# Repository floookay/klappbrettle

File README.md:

> [!CAUTION]
> This is still a work in progress and not yet fully tested! I messed up my last order from Mouser and need to get the missing components the next time I get to order.

# klappbrettle

a 40% ortho keyboard with a hinge

## design

I love using ortho keyboards but non-split ortho keyboards are getting uncomfortable for me fast so I thought about adding a hinge at the top.

It kind of resembles a starter clapper so that's where it got its name and athletics theme.

## pcb

PCBWay ([PCBWay.com](https://pcbway.com)) kindly offered to sponsor the pcb for this project that's why I got my hands on the pcbs within almost a week after ordering.  
The order process is straight forward and you also get an instant quote before ordering. After placing the order a technician checked and corrected the drill holes of the mouse bits within a few hours and the pcb was sent to manufacturing.
I'm impressed with the speed an quality of the pcb, see below:

The pcb is a two panel design where both sides are connected via a 10 pin JST connector. It's powered by a RP2040 microcontroller so there is plenty of flash storage. You can clip off the mod columns or the outer thumb key if want to. There are also extra holes where you can put grommets so the switches don't pop out of the 3mm plate.

- [x] complete the pcb design
- [ ] order missing components and solder

## case

The case is a 3mm acryl sandwich style case with a hinge to connect the halves and route the cable through. The hinge can be either 3d printed or can be 3mm acryl as well. I still need to test what works best, so far I only have a 3d printed prototype at hand.

- [x] complete the acrylic case design
- [ ] make the bottom plates look a bit nicer
- [ ] prepare dxf files and variants for laser cutting

## firmware

This will be powered by QMK but the firmware isn't ready yet.

- [x] finish [qmk firmware](https://github.com/floookay/qmk_firmware/tree/klappbrettle)
- [ ] add vial support

## acknowledgements

Huge thanks to PCBWay for offering to sponsor this project, hlord2000 for their [RP2040 KiCAD template](https://github.com/hlord2000/Ohmbedded-RP2040-PCB-Template) as well as the ClackTales community for helping me with the theme.

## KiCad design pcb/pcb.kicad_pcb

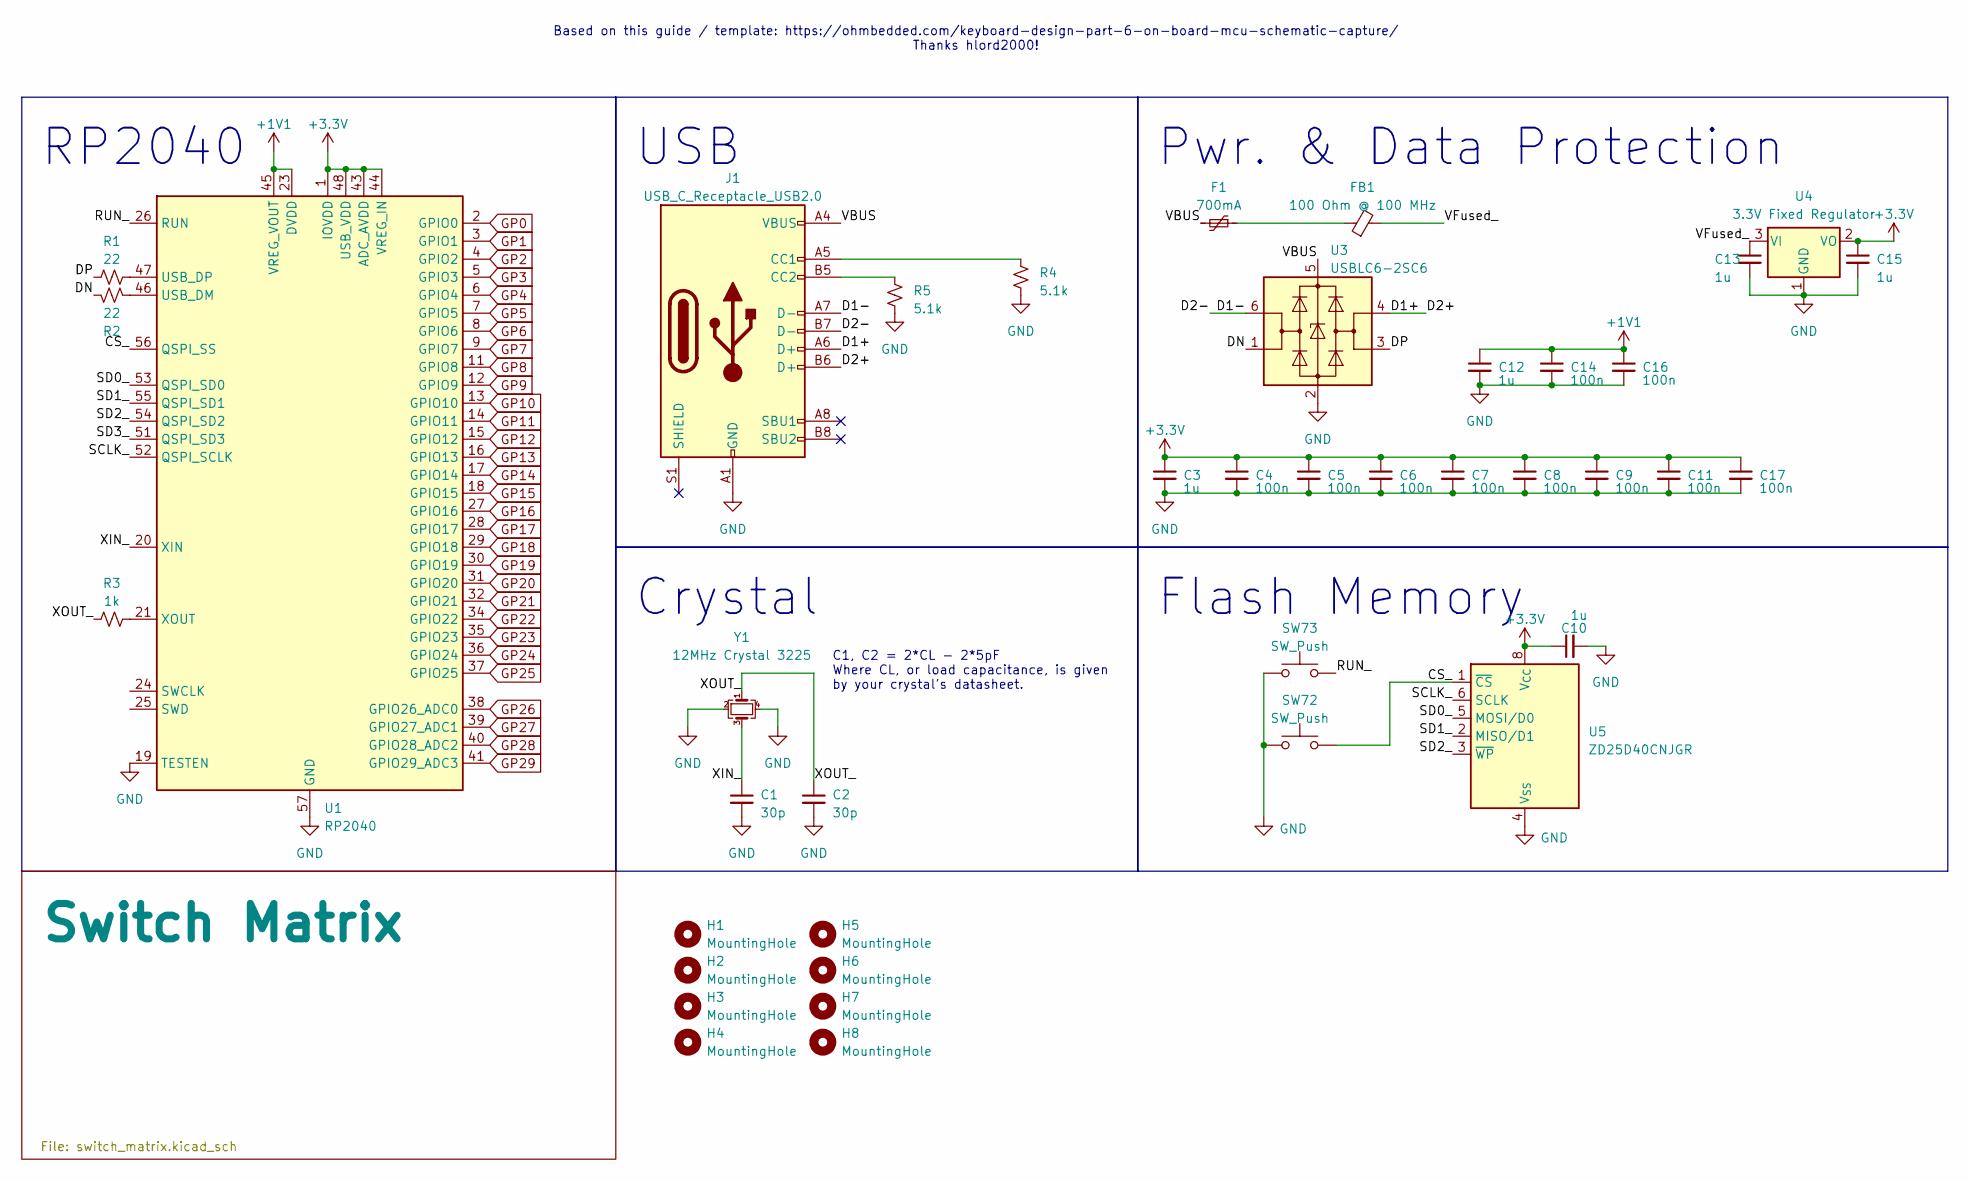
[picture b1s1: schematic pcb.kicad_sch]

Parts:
C1, C2: 30p; C_0402_1005Metric; LCSC C1562
C3, C10, C12, C13, C15: 1u; C_0402_1005Metric; LCSC C52923
C4, C5, C6, C7, C8, C9, C11, C14, C16, C17: 100n; C_0402_1005Metric; LCSC C1525
F1: 700mA; Fuse_0402_1005Metric; LCSC C914086
FB1: 100 Ohm @ 100 MHz; L_0402_1005Metric; LCSC C85812
H1, H2, H3, H4, H5, H6, H7, H8: MountingHole; spacer_hole_4mm
J1: USB_C_Receptacle_USB2.0; USB_C_Receptacle_GCT_USB4110
R1, R2: 22; R_0402_1005Metric; LCSC C25152
R3: 1k; R_0402_1005Metric; LCSC C106235
R4, R5: 5.1k; R_0402_1005Metric; LCSC C25905
SW72, SW73: SW_Push; SW_SPST_SKQG_WithoutStem; LCSC C115351
U1: RP2040; QFN-56-1EP_7x7mm_P0.4mm_EP3.2x3.2mm_ThermalVias; LCSC C2040
U3: USBLC6-2SC6; SOT-23-6; LCSC C558442
U4: 3.3V Fixed Regulator; TSOT-23; LCSC C150715
U5: ZD25D40CNJGR; USON-8_1.5x1.5mm_P0.45mm; LCSC C3646778
Y1: 12MHz Crystal 3225; Crystal_SMD_3225-4Pin_3.2x2.5mm; LCSC C9002

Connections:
+1V1: C12.1, C14.1, C16.1, U1.23 (DVDD), U1.45 (VREG_VOUT), U1.50 (DVDD)
+3.3V: C3.1, C4.1, C5.1, C6.1, C7.1, C8.1, C9.1, C10.1, C11.1, C15.1, C17.1, U1.1 (IOVDD), U1.10 (IOVDD), U1.22 (IOVDD), U1.33 (IOVDD), U1.42 (IOVDD), U1.43 (ADC_AVDD), U1.44 (VREG_IN), U1.48 (USB_VDD), U1.49 (IOVDD), U4.2 (VO), U5.8 (V_{CC})
/CS_: SW72.2, U1.56 (QSPI_SS), U5.1 (~CS)
/D1+: J1.A6 (D+), J1.B6 (D+), U3.4 (I/O2)
/D1-: J1.A7 (D-), J1.B7 (D-), U3.6 (I/O1)
/DN: R2.2, U3.1 (I/O1)
/DP: R1.1, U3.3 (I/O2)
/RUN_: SW73.2, U1.26 (RUN)
/SCLK_: U1.52 (QSPI_SCLK), U5.6 (SCLK)
/SD0_: U1.53 (QSPI_SD0), U5.5 (MOSI/D0)
/SD1_: U1.55 (QSPI_SD1), U5.2 (MISO/D1)
/SD2_: U1.54 (QSPI_SD2), U5.3 (~WP)
/SD3_: U1.51 (QSPI_SD3)
/VBUS: F1.2, J1.A4 (VBUS), J1.A9 (VBUS), J1.B4 (VBUS), J1.B9 (VBUS), U3.5 (VBUS)
/VFused_: C13.1, FB1.2, U4.3 (VI)
/XIN_: C1.1, U1.20 (XIN), Y1.3
/XOUT_: C2.1, R3.1, Y1.1
GND: C1.2, C2.2, C3.2, C4.2, C5.2, C6.2, C7.2, C8.2, C9.2, C10.2, C11.2, C12.2, C13.2, C14.2, C15.2, C16.2, C17.2, J1.A1 (GND), J1.A12 (GND), J1.B1 (GND), J1.B12 (GND), R4.1, R5.1, SW72.1, SW73.1, U1.19 (TESTEN), U1.57 (GND), U3.2 (GND), U4.1 (GND), U5.4 (V_{SS}), U5.9 (PAD/V_{SS}), Y1.2, Y1.4
GP0: U1.2 (GPIO0)
GP1: U1.3 (GPIO1); also elsewhere on the board
GP2: U1.4 (GPIO2); also elsewhere on the board
GP3: U1.5 (GPIO3); also elsewhere on the board
GP4: U1.6 (GPIO4); also elsewhere on the board
GP5: U1.7 (GPIO5); also elsewhere on the board
GP6: U1.8 (GPIO6); also elsewhere on the board
GP7: U1.9 (GPIO7)
GP8: U1.11 (GPIO8)
GP9: U1.12 (GPIO9)
GP10: U1.13 (GPIO10)
GP11: U1.14 (GPIO11); also elsewhere on the board
GP12: U1.15 (GPIO12); also elsewhere on the board
GP13: U1.16 (GPIO13); also elsewhere on the board
GP14: U1.17 (GPIO14); also elsewhere on the board
GP15: U1.18 (GPIO15); also elsewhere on the board
GP16: U1.27 (GPIO16); also elsewhere on the board
GP17: U1.28 (GPIO17)
GP18: U1.29 (GPIO18)
GP19: U1.30 (GPIO19)
GP20: U1.31 (GPIO20)
GP21: U1.32 (GPIO21)
GP22: U1.34 (GPIO22)
GP23: U1.35 (GPIO23); also elsewhere on the board
GP24: U1.36 (GPIO24); also elsewhere on the board
GP25: U1.37 (GPIO25)
GP26: U1.38 (GPIO26_ADC0)
GP27: U1.39 (GPIO27_ADC1)
GP28: U1.40 (GPIO28_ADC2); also elsewhere on the board
GP29: U1.41 (GPIO29_ADC3); also elsewhere on the board
unnamed: F1.1, FB1.1
unnamed: J1.A5 (CC1), R4.2
unnamed: J1.B5 (CC2), R5.2
unnamed: R2.1, U1.46 (USB_DM)
unnamed: R1.2, U1.47 (USB_DP)
unnamed: R3.2, U1.21 (XOUT)

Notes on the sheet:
Flash Memory
Pwr. & Data Protection
Based on this guide / template: https://ohmbedded.com/keyboard-design-part-6-on-board-mcu-schematic-capture/ Thanks hlord2000!
C1, C2 = 2*CL - 2*5pF Where CL, or load capacitance, is given by your crystal's datasheet.
Crystal
RP2040
USB

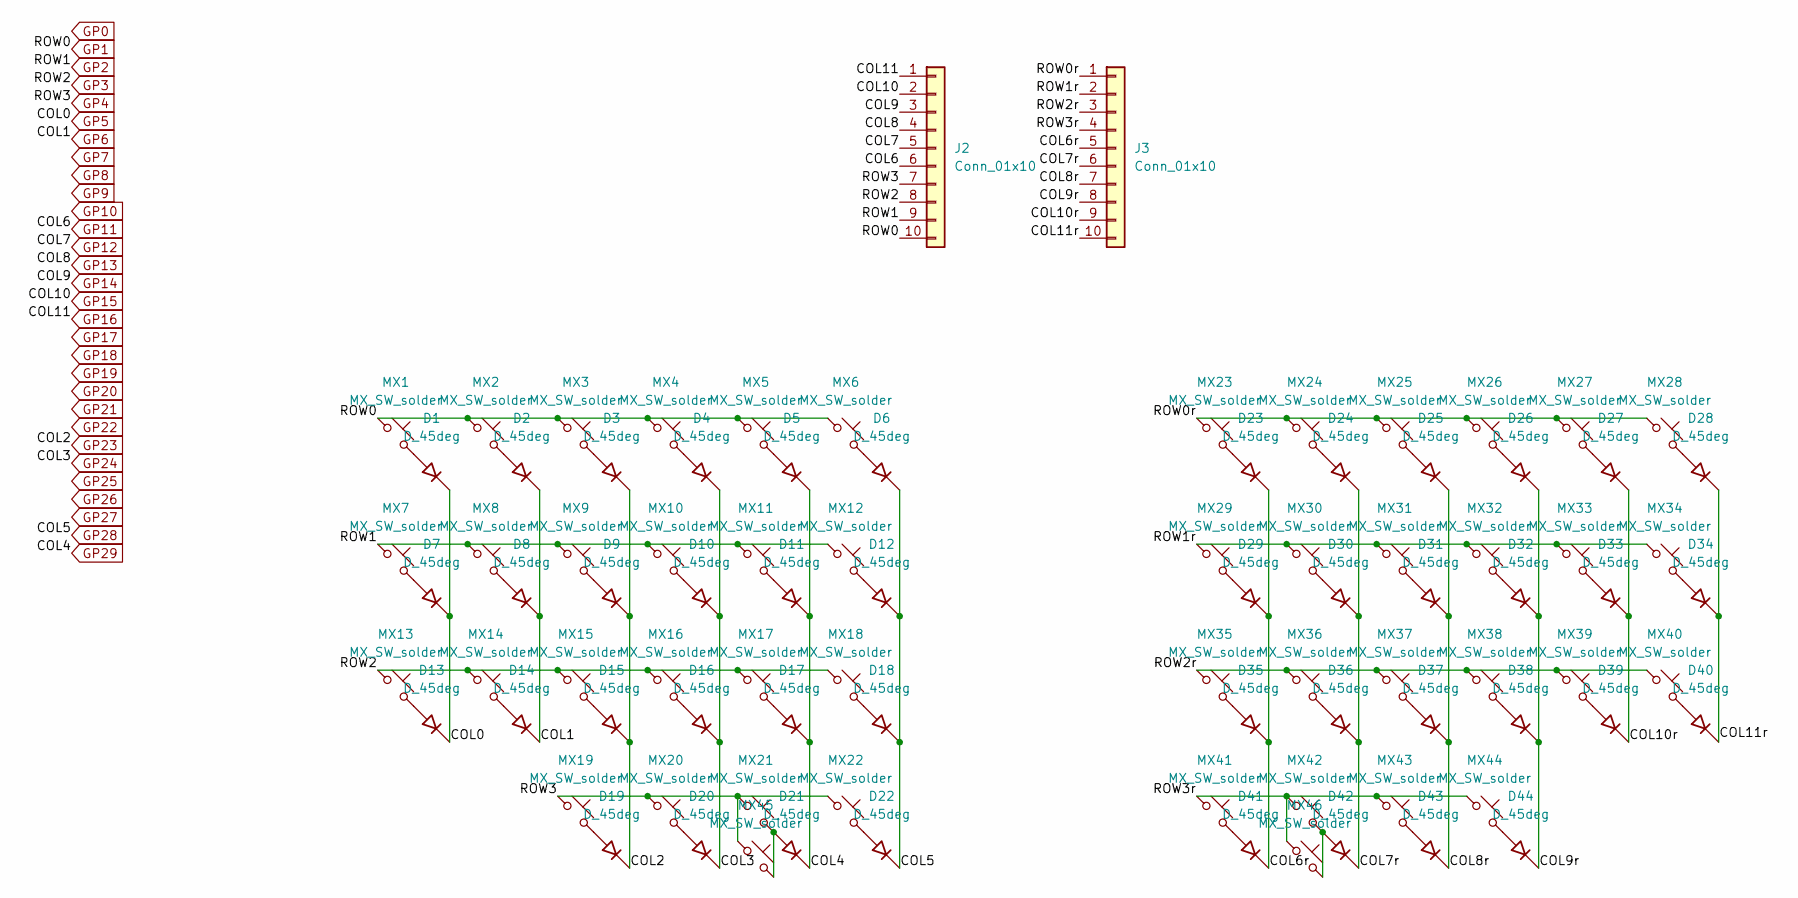
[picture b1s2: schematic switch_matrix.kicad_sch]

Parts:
D1, D2, D3, D4, D5, D6, D7, D8, D9, D10, D11, D12, D13, D14, D15, D16, D17, D18, D19, D20, D21, D22, D23, D24, D25, D26, D27, D28, D29, D30, D31, D32, D33, D34, D35, D36, D37, D38, D39, D40, D41, D42, D43, D44: D_45deg; D_SOD-123-minimal
J2, J3: Conn_01x10; JST_GH_SM10B-GHS-TB_1x10-1MP_P1.25mm_Horizontal
MX1, MX2, MX3, MX4, MX5, MX6, MX7, MX8, MX9, MX10, MX11, MX12, MX13, MX14, MX15, MX16, MX17, MX18, MX19, MX20, MX21, MX22, MX23, MX24, MX25, MX26, MX27, MX28, MX29, MX30, MX31, MX32, MX33, MX34, MX35, MX36, MX37, MX38, MX39, MX40, MX41, MX42, MX43, MX44, MX45, MX46: MX_SW_solder; SW_MX_1u

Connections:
/Switch Matrix/COL6r: D23.1 (K), D29.1 (K), D35.1 (K), D41.1 (K), J3.5
/Switch Matrix/COL7r: D24.1 (K), D30.1 (K), D36.1 (K), D42.1 (K), J3.6
/Switch Matrix/COL8r: D25.1 (K), D31.1 (K), D37.1 (K), D43.1 (K), J3.7
/Switch Matrix/COL9r: D26.1 (K), D32.1 (K), D38.1 (K), D44.1 (K), J3.8
/Switch Matrix/COL10r: D27.1 (K), D33.1 (K), D39.1 (K), J3.9
/Switch Matrix/COL11r: D28.1 (K), D34.1 (K), D40.1 (K), J3.10
/Switch Matrix/ROW0r: J3.1, MX23.1, MX24.1, MX25.1, MX26.1, MX27.1, MX28.1
/Switch Matrix/ROW1r: J3.2, MX29.1, MX30.1, MX31.1, MX32.1, MX33.1, MX34.1
/Switch Matrix/ROW2r: J3.3, MX35.1, MX36.1, MX37.1, MX38.1, MX39.1, MX40.1
/Switch Matrix/ROW3r: J3.4, MX41.1, MX42.1, MX43.1, MX44.1, MX46.1
GP1: J2.10, MX1.1, MX2.1, MX3.1, MX4.1, MX5.1, MX6.1; also elsewhere on the board
GP2: J2.9, MX7.1, MX8.1, MX9.1, MX10.1, MX11.1, MX12.1; also elsewhere on the board
GP3: J2.8, MX13.1, MX14.1, MX15.1, MX16.1, MX17.1, MX18.1; also elsewhere on the board
GP4: J2.7, MX19.1, MX20.1, MX21.1, MX22.1, MX45.1; also elsewhere on the board
GP5: D1.1 (K), D7.1 (K), D13.1 (K); also elsewhere on the board
GP6: D2.1 (K), D8.1 (K), D14.1 (K); also elsewhere on the board
GP11: J2.6; also elsewhere on the board
GP12: J2.5; also elsewhere on the board
GP13: J2.4; also elsewhere on the board
GP14: J2.3; also elsewhere on the board
GP15: J2.2; also elsewhere on the board
GP16: J2.1; also elsewhere on the board
GP23: D3.1 (K), D9.1 (K), D15.1 (K), D19.1 (K); also elsewhere on the board
GP24: D4.1 (K), D10.1 (K), D16.1 (K), D20.1 (K); also elsewhere on the board
GP28: D6.1 (K), D12.1 (K), D18.1 (K), D22.1 (K); also elsewhere on the board
GP29: D5.1 (K), D11.1 (K), D17.1 (K), D21.1 (K); also elsewhere on the board
unnamed: D1.2 (A), MX1.2
unnamed: D2.2 (A), MX2.2
unnamed: D3.2 (A), MX3.2
unnamed: D4.2 (A), MX4.2
unnamed: D5.2 (A), MX5.2
unnamed: D6.2 (A), MX6.2
unnamed: D7.2 (A), MX7.2
unnamed: D8.2 (A), MX8.2
unnamed: D9.2 (A), MX9.2
unnamed: D10.2 (A), MX10.2
unnamed: D11.2 (A), MX11.2
unnamed: D12.2 (A), MX12.2
unnamed: D13.2 (A), MX13.2
unnamed: D14.2 (A), MX14.2
unnamed: D15.2 (A), MX15.2
unnamed: D16.2 (A), MX16.2
unnamed: D17.2 (A), MX17.2
unnamed: D18.2 (A), MX18.2
unnamed: D19.2 (A), MX19.2
unnamed: D20.2 (A), MX20.2
unnamed: D21.2 (A), MX21.2, MX45.2
unnamed: D22.2 (A), MX22.2
unnamed: D23.2 (A), MX23.2
unnamed: D24.2 (A), MX24.2
unnamed: D25.2 (A), MX25.2
unnamed: D26.2 (A), MX26.2
unnamed: D27.2 (A), MX27.2
unnamed: D28.2 (A), MX28.2
unnamed: D29.2 (A), MX29.2
unnamed: D30.2 (A), MX30.2
unnamed: D31.2 (A), MX31.2
unnamed: D32.2 (A), MX32.2
unnamed: D33.2 (A), MX33.2
unnamed: D34.2 (A), MX34.2
unnamed: D35.2 (A), MX35.2
unnamed: D36.2 (A), MX36.2
unnamed: D37.2 (A), MX37.2
unnamed: D38.2 (A), MX38.2
unnamed: D39.2 (A), MX39.2
unnamed: D40.2 (A), MX40.2
unnamed: D41.2 (A), MX41.2
unnamed: D42.2 (A), MX42.2, MX46.2
unnamed: D43.2 (A), MX43.2
unnamed: D44.2 (A), MX44.2

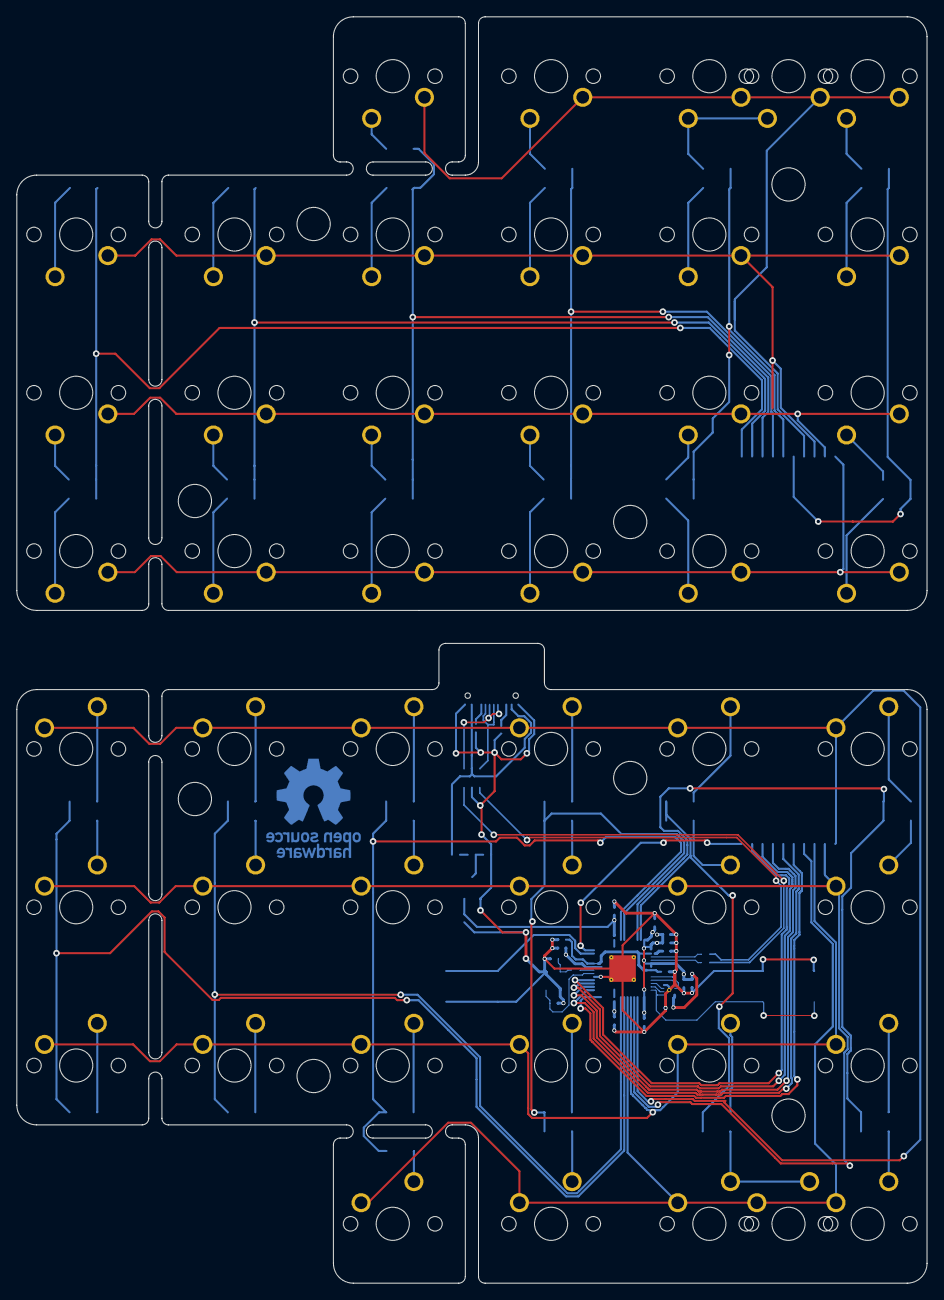
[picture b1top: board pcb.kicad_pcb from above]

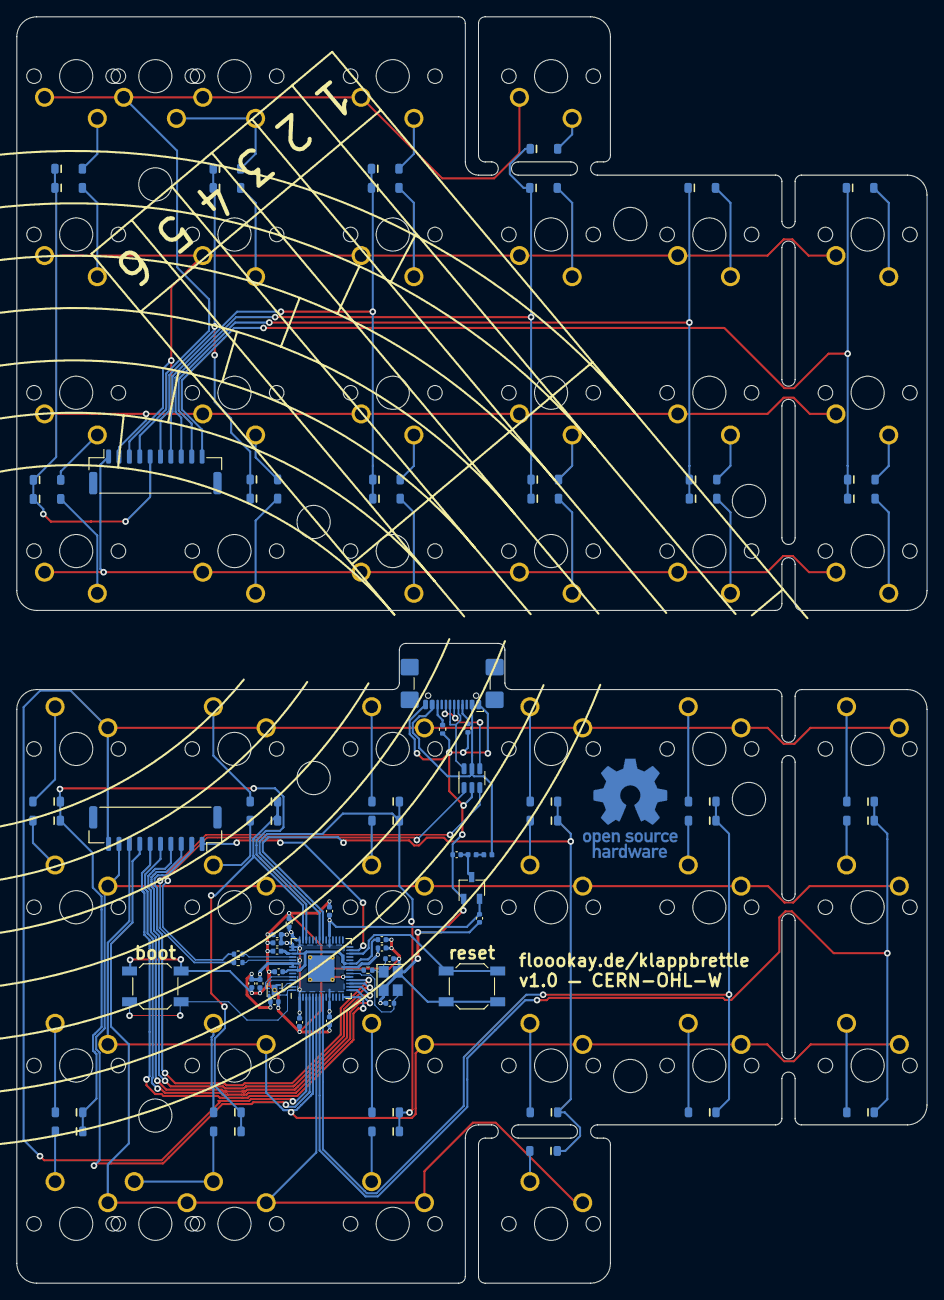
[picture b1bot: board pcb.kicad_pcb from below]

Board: 4 copper layers, 109.5 x 152.4 mm, 132 parts (78 on the bottom side), 93 nets.

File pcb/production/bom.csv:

Designator,Footprint,Quantity,Value,LCSC Part #
"C1, C2",0402,2,30p,C1562
"C10, C12, C13, C15, C3",0402,5,1u,C52923
"C11, C14, C16, C17, C4, C5, C6, C7, C8, C9",0402,10,100n,C1525
"D1, D10, D11, D12, D13, D14, D15, D16, D17, D18, D19, D2, D20, D21, D22, D23, D24, D25, D26, D27, D28, D29, D3, D30, D31, D32, D33, D34, D35, D36, D37, D38, D39, D4, D40, D41, D42, D43, D44, D5, D6, D7, D8, D9",D_SOD-123-minimal,44,D_45deg,
F1,0402,1,700mA,C914086
FB1,0402,1,100 Ohm @ 100 MHz,C85812
J1,USB_C_Receptacle_GCT_USB4110,1,USB_C_Receptacle_USB2.0,C9002
"J2, J3",JST_GH_SM10B-GHS-TB_1x10-1MP_P1.25mm_Horizontal,2,Conn_01x10,C2683602
"MX1, MX10, MX11, MX12, MX13, MX14, MX15, MX16, MX17, MX18, MX19, MX2, MX20, MX21, MX22, MX23, MX24, MX25, MX26, MX27, MX28, MX29, MX3, MX30, MX31, MX32, MX33, MX34, MX35, MX36, MX37, MX38, MX39, MX4, MX40, MX41, MX42, MX43, MX44, MX45, MX46, MX5, MX6, MX7, MX8, MX9",SW_MX_1u,46,MX_SW_solder,
"R1, R2",0402,2,22,C25152
R3,0402,1,1k,C106235
"R4, R5",0402,2,5.1k,C25905
"S1, S2",STAB_MX_P_2u,2,MX_stab,
"SW72, SW73",SW_SPST_SKQG_WithoutStem,2,SW_Push,C115351
U1,QFN-56-1EP_7x7mm_P0.4mm_EP3.2x3.2mm_ThermalVias,1,RP2040,C2040
U3,SOT-23-6,1,USBLC6-2SC6,C558442
U4,TSOT-23,1,3.3V Fixed Regulator,C150715
U5,USON-8_1.5x1.5mm_P0.45mm,1,ZD25D40CNJGR,C3646778
Y1,Crystal_SMD_3225-4Pin_3.2x2.5mm,1,12MHz Crystal 3225,C9002

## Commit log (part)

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2025-02-15 added license
2025-02-15 added prototype of left half
2025-02-24 added right half
2025-02-24 updated gitignore
2025-02-25 added pcb
2025-03-07 added basic layout
2025-03-14 fixed connections
2025-03-16 imported template for rp2040 components
2025-03-16 updated case design with stepped layers
2025-03-16 added jst cutouts
2025-03-16 enlarged standoffs
2025-03-21 added usb cutout and hinge pin
2025-03-21 added some more routing
2025-03-21 added case stl files
2025-03-22 added bottom silk draft
2025-03-23 redid routing
2025-04-12 added silk, panels and stabs
2025-04-12 turned 2 spacers around because of the stabs
2025-07-20 added latest files
2025-07-20 gif test
2025-07-20 fixed typo
2025-07-20 fixed another typo
2026-05-14 fixed positions

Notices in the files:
pcb/pcb.kicad_pcb:
v1.0 — CERN-OHL-W
